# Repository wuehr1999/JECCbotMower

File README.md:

# JECCbotMower

Implementation of JECCbot modifications for lawn mowing robot

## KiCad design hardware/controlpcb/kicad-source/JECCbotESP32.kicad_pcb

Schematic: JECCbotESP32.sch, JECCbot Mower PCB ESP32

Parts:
C1: 100n; C_0603
C2, C3: 10uF; C_0603
C47: 100nF; C_0603
D1: Led_Small; LED_0603
R1, R3, R4, R5: 10k; R_0603
R2: 220; R_0603
R7: DNI; R_0603
SW1, SW2: TAST_VER; WE_430182050816
U1: ESP32_WROOM_32; ESP32-WROOM-32
U2, U3: 74xx4052; SOIC-16_3.9x9.9mm_Pitch1.27mm
U4: TCA9534; SOIC-16_7.5x10.3mm_Pitch1.27mm
U5: ADS1015; MSOP-10_3x3mm_Pitch0.5mm

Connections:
+3V3: C2.1, C3.1, C47.1, D1.2 (A), R1.1, R3.1, R4.1, R5.1, U1.2 (3V3), U2.16, U3.16, U4.16 (VCC), U5.8 (VCC); also elsewhere on the board
/INT: R5.2, U1.6 (IO34), U4.13 (INT)
/MUX1_A: U1.13 (IO14), U2.10
/MUX1_B: U1.14 (IO12), U2.9
/MUX2_A: U1.16 (IO13), U3.10
/MUX2_B: U1.23 (IO15), U3.9
/MUX2_COM1: U1.26 (IO4), U3.13
/MUX2_COM2: U1.7 (IO35), U3.3
/RX: U1.27 (IO16), U2.13
/TX: U1.28 (IO17), U2.3
ADC: U5.7 (AIN3); also elsewhere on the board
BOOT: SW1.1, SW1.3, U1.25 (IO0); also elsewhere on the board
CS: U4.4 (P0); also elsewhere on the board
DRIVE_BEMF1: U1.4 (SENSOR_VP); also elsewhere on the board
DRIVE_BEMF2: U1.5 (SENSOR_VN); also elsewhere on the board
DRIVE_INH: U1.12 (IO27); also elsewhere on the board
DRIVE_IS: U5.4 (AIN0); also elsewhere on the board
DRIVE_PWM1: U1.8 (IO32); also elsewhere on the board
DRIVE_PWM2: U1.9 (IO33); also elsewhere on the board
DRIVE_PWM3: U1.10 (IO25); also elsewhere on the board
DRIVE_PWM4: U1.11 (IO26); also elsewhere on the board
EM_STOP: U4.5 (P1); also elsewhere on the board
GND: C1.2, C2.2, C3.2, C47.2, R2.2, R7.2, SW1.2, SW1.4, SW2.2, SW2.4, U1.1 (GND), U1.15 (GND), U1.38 (GND), U1.39 (P_GND), U2.6, U2.7, U2.8, U3.6, U3.7, U3.8, U4.1 (A0), U4.2 (A1), U4.3 (A2), U4.8 (GND), U5.3 (GND); also elsewhere on the board
GPIO0: U4.9 (P4); also elsewhere on the board
GPIO1: U4.10 (P5); also elsewhere on the board
GPIO2: U4.11 (P6); also elsewhere on the board
GPIO3: U4.12 (P7); also elsewhere on the board
GPIO5: U1.29 (IO5); also elsewhere on the board
INT_BNO055: U4.7 (P3); also elsewhere on the board
KNIFE_INH: U4.6 (P2); also elsewhere on the board
KNIFE_IS: U5.5 (AIN1); also elsewhere on the board
KNIFE_PWM: U1.24 (IO2); also elsewhere on the board
MISO: U1.31 (IO19); also elsewhere on the board
MOSI: U1.37 (IO23); also elsewhere on the board
unnamed: D1.1 (K), R2.1
unnamed: R7.1, U5.1 (ADDR)
RESET: C1.1, R1.2, SW2.1, SW2.3, U1.3 (EN); also elsewhere on the board
RX0: U2.12; also elsewhere on the board
RX0_USB: U1.34 (RXD0); also elsewhere on the board
RX1: U2.14; also elsewhere on the board
RX2: U2.15; also elsewhere on the board
RX3: U2.11; also elsewhere on the board
SCK: U1.30 (IO18); also elsewhere on the board
SCL: R4.2, U1.36 (IO22), U4.14 (SCL), U5.10 (SCL); also elsewhere on the board
SDA: R3.2, U1.33 (IO21), U4.15 (SDA), U5.9 (SDA); also elsewhere on the board
TX0: U2.1; also elsewhere on the board
TX0_USB: U1.35 (TXD0); also elsewhere on the board
TX1: U2.5; also elsewhere on the board
TX2: U2.2; also elsewhere on the board
TX3: U2.4; also elsewhere on the board
U1_ECHO: U3.1; also elsewhere on the board
U1_TRIG: U3.12; also elsewhere on the board
U2_ECHO: U3.5; also elsewhere on the board
U2_TRIG: U3.14; also elsewhere on the board
U3_ECHO: U3.2; also elsewhere on the board
U3_TRIG: U3.15; also elsewhere on the board
VBAT_SENSE: U5.6 (AIN2); also elsewhere on the board

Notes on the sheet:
onboard flash

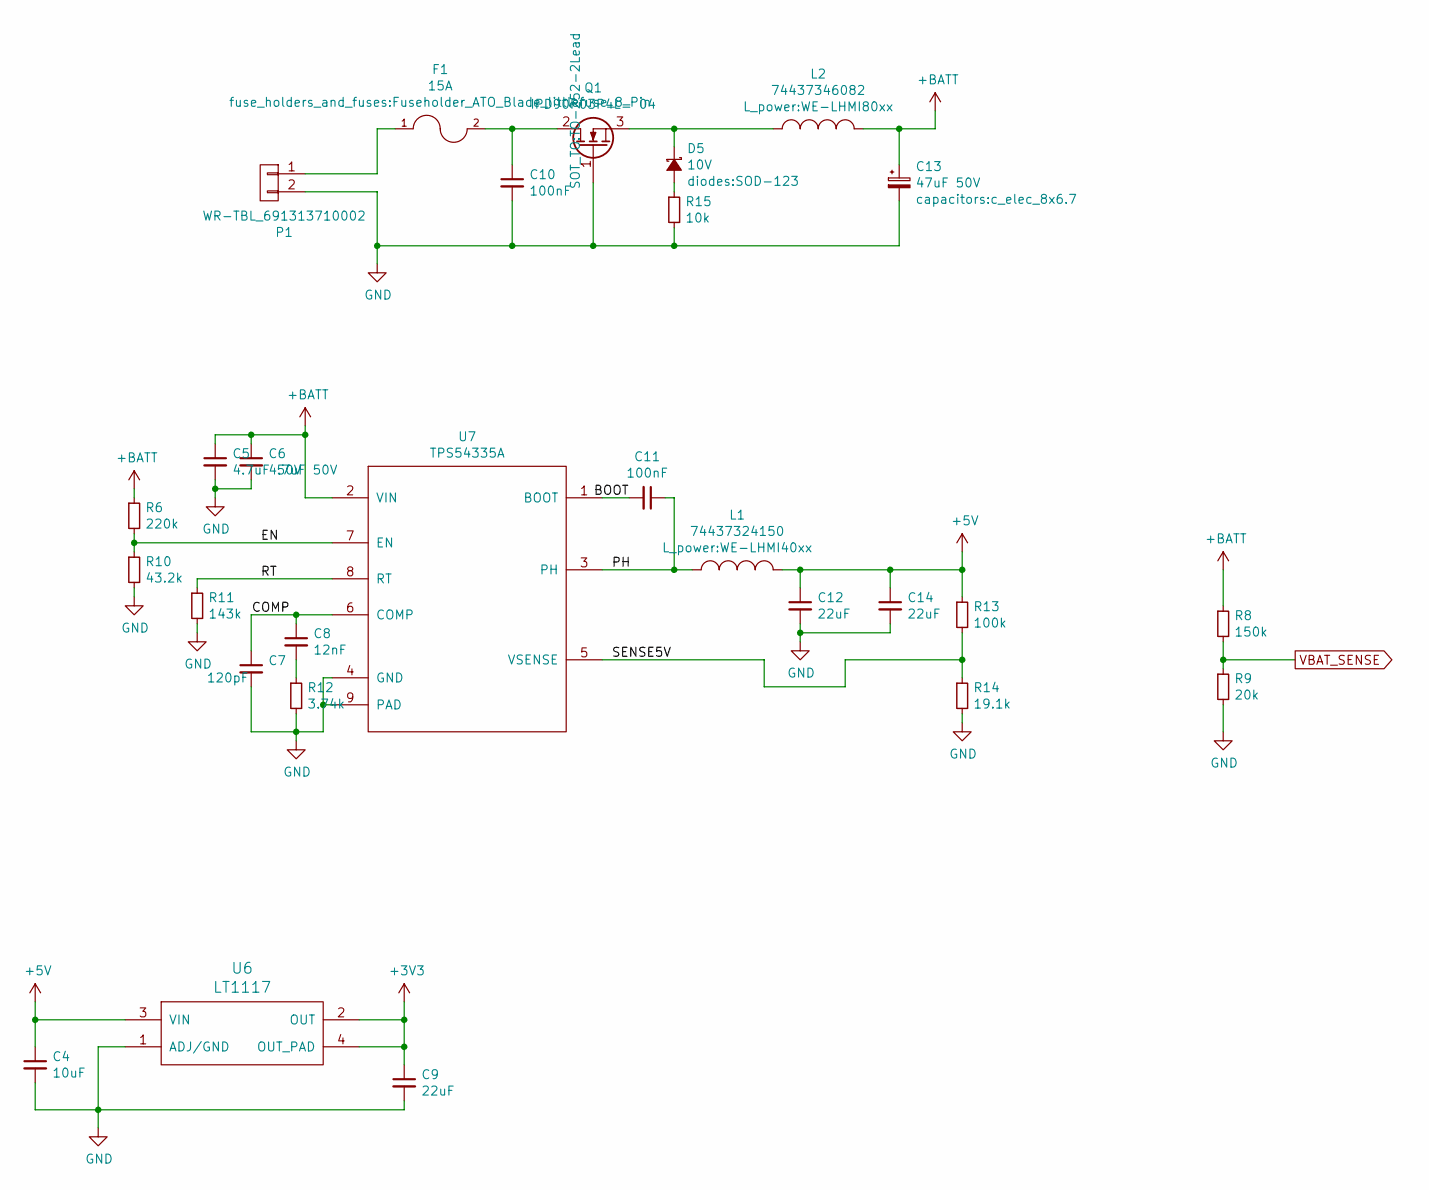
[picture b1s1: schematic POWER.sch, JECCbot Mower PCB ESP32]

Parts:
C4: 10uF; C_1206
C5, C6: 4.7uF 50V; C_1206
C7: 120pF; C_0603
C8: 12nF; C_0603
C9, C12, C14: 22uF; C_1206
C10, C11: 100nF; C_0603
C13: 47uF 50V; c_elec_8x6.7
D5: 10V; SOD-123
F1: 15A; Fuseholder_ATO_Blade_littlefuse_8_Pin
L1: 74437324150; WE-LHMI40xx
L2: 74437346082; WE-LHMI80xx
P1: WR-TBL_691313710002
Q1: IPD90P03P4L- 04; TO-252-2Lead
R6: 220k; R_0603
R8: 150k; R_0603
R9: 20k; R_0603
R10: 43.2k; R_0603
R11: 143k; R_0603
R12: 3.74k; R_0603
R13: 100k; R_0603
R14: 19.1k; R_0603
R15: 10k; R_0603
U6: LT1117; SOT-223
U7: TPS54335A; SOIC-8-1EP_3.9x4.9mm_Pitch1.27mm

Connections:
+3V3: C9.1, U6.2 (OUT), U6.4 (OUT_PAD); also elsewhere on the board
+5V: C4.1, C12.1, C14.1, L1.2, R13.1, U6.3 (VIN); also elsewhere on the board
+BATT: C5.1, C6.1, C13.1, L2.2, R6.1, R8.1, U7.2 (VIN); also elsewhere on the board
/POWER/COMP: C7.1, C8.1, U7.6 (COMP)
/POWER/EN: R6.2, R10.1, U7.7 (EN)
/POWER/PH: C11.1, L1.1, U7.3 (PH)
/POWER/RT: R11.1, U7.8 (RT)
/POWER/SENSE5V: R13.2, R14.1, U7.5 (VSENSE)
GND: C4.2, C5.2, C6.2, C7.2, C9.2, C10.2, C12.2, C13.2, C14.2, P1.2, Q1.1 (G), R9.2, R10.2, R11.2, R12.2, R14.2, R15.2, U6.1 (ADJ/GND), U7.4 (GND), U7.9 (PAD); also elsewhere on the board
unnamed: C8.2, R12.1
unnamed: C10.1, F1.2, Q1.2 (D)
unnamed: C11.2, U7.1 (BOOT)
unnamed: D5.1 (K), L2.1, Q1.3 (S)
unnamed: D5.2 (A), R15.1
unnamed: F1.1, P1.1
VBAT_SENSE: R8.2, R9.1; also elsewhere on the board

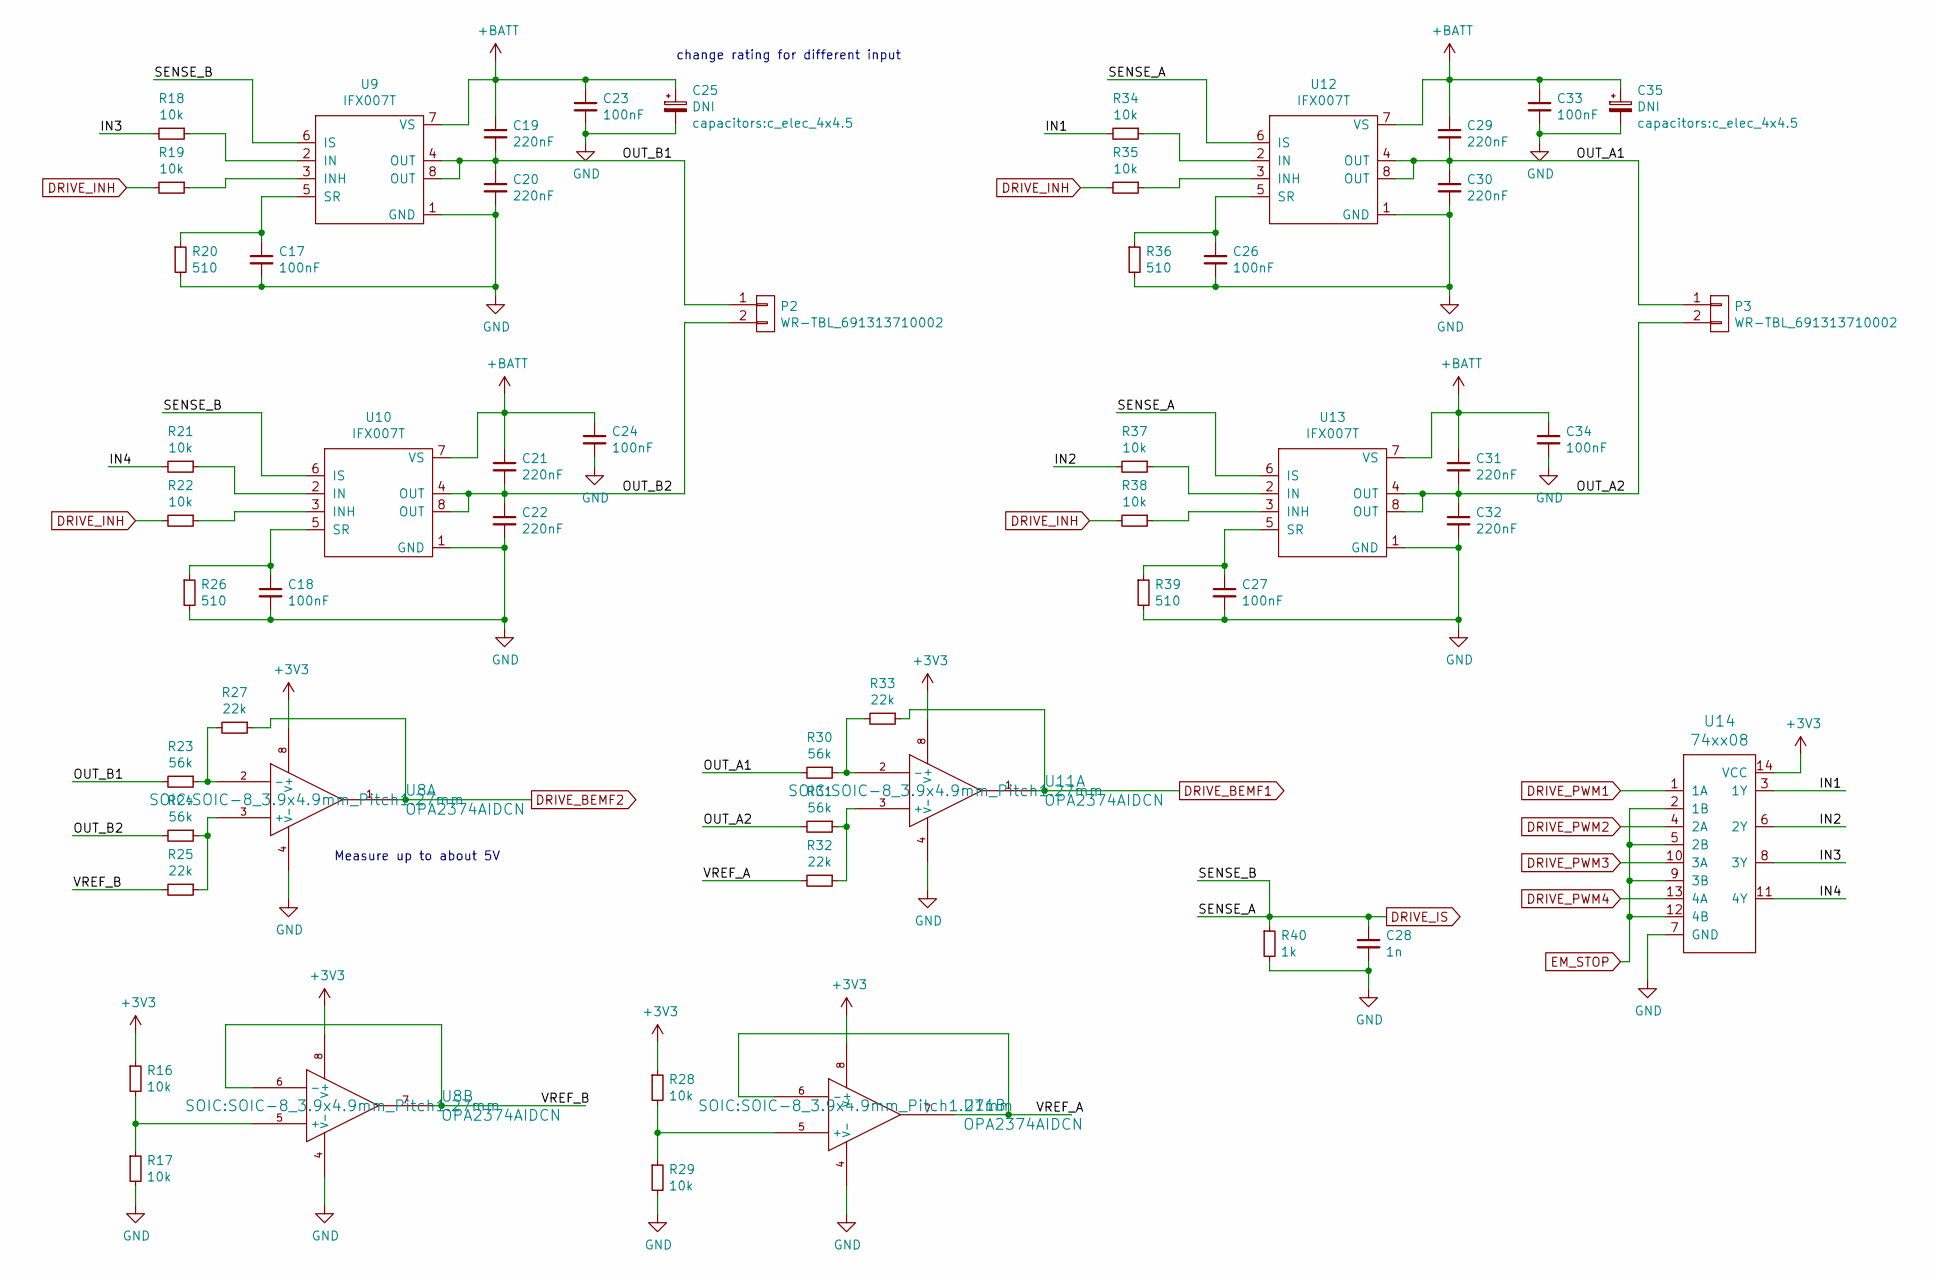
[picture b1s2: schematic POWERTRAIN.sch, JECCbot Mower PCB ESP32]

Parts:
C17, C18, C23, C24, C26, C27, C33, C34: 100nF; C_0603
C19, C20, C21, C22, C29, C30, C31, C32: 220nF; C_0603
C25, C35: DNI; c_elec_4x4.5
C28: 1n; C_0603
P2, P3: WR-TBL_691313710002
R16, R17, R18, R19, R21, R22, R28, R29, R34, R35, R37, R38: 10k; R_0603
R20, R26, R36, R39: 510; R_0603
R23, R24, R30, R31: 56k; R_0603
R25, R27, R32, R33: 22k; R_0603
R40: 1k; R_0603
U8, U11: OPA2374AIDCN; SOIC-8_3.9x4.9mm_Pitch1.27mm
U9, U10, U12, U13: IFX007T; TO-263-7Lead
U14: 74xx08; SOIC-14_3.9x8.7mm_Pitch1.27mm

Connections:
+3V3: R16.1, R28.1, U8.8 (V+), U11.8 (V+), U14.14 (VCC); also elsewhere on the board
+BATT: C19.1, C21.1, C23.1, C24.1, C25.1, C29.1, C31.1, C33.1, C34.1, C35.1, U9.7 (VS), U10.7 (VS), U12.7 (VS), U13.7 (VS); also elsewhere on the board
/POWERTRAIN/IN1: R34.2, U14.3 (1Y)
/POWERTRAIN/IN2: R37.2, U14.6 (2Y)
/POWERTRAIN/IN3: R18.2, U14.8 (3Y)
/POWERTRAIN/IN4: R21.2, U14.11 (4Y)
/POWERTRAIN/OUT_A1: C29.2, C30.1, P3.1, R30.2, U12.4 (OUT), U12.8 (OUT)
/POWERTRAIN/OUT_A2: C31.2, C32.1, P3.2, R31.2, U13.4 (OUT), U13.8 (OUT)
/POWERTRAIN/OUT_B1: C19.2, C20.1, P2.1, R23.2, U9.4 (OUT), U9.8 (OUT)
/POWERTRAIN/OUT_B2: C21.2, C22.1, P2.2, R24.2, U10.4 (OUT), U10.8 (OUT)
/POWERTRAIN/VREF_A: R32.2, U11.6 (-), U11.7
/POWERTRAIN/VREF_B: R25.2, U8.6 (-), U8.7
DRIVE_BEMF1: R33.1, U11.1; also elsewhere on the board
DRIVE_BEMF2: R27.1, U8.1; also elsewhere on the board
DRIVE_INH: R19.2, R22.2, R35.2, R38.2; also elsewhere on the board
DRIVE_IS: C28.1, R40.1, U9.6 (IS), U10.6 (IS), U12.6 (IS), U13.6 (IS); also elsewhere on the board
DRIVE_PWM1: U14.1 (1A); also elsewhere on the board
DRIVE_PWM2: U14.4 (2A); also elsewhere on the board
DRIVE_PWM3: U14.10 (3A); also elsewhere on the board
DRIVE_PWM4: U14.13 (4A); also elsewhere on the board
EM_STOP: U14.2 (1B), U14.5 (2B), U14.9 (3B), U14.12 (4B); also elsewhere on the board
GND: C17.2, C18.2, C20.2, C22.2, C23.2, C24.2, C25.2, C26.2, C27.2, C28.2, C30.2, C32.2, C33.2, C34.2, C35.2, R17.2, R20.2, R26.2, R29.2, R36.2, R39.2, R40.2, U8.4 (V-), U9.1 (GND), U10.1 (GND), U11.4 (V-), U12.1 (GND), U13.1 (GND), U14.7 (GND); also elsewhere on the board
unnamed: C17.1, R20.1, U9.5 (SR)
unnamed: C18.1, R26.1, U10.5 (SR)
unnamed: C26.1, R36.1, U12.5 (SR)
unnamed: C27.1, R39.1, U13.5 (SR)
unnamed: R16.2, R17.1, U8.5 (+)
unnamed: R18.1, U9.2 (IN)
unnamed: R19.1, U9.3 (INH)
unnamed: R21.1, U10.2 (IN)
unnamed: R22.1, U10.3 (INH)
unnamed: R23.1, R27.2, U8.2 (-)
unnamed: R24.1, R25.1, U8.3 (+)
unnamed: R28.2, R29.1, U11.5 (+)
unnamed: R30.1, R33.2, U11.2 (-)
unnamed: R31.1, R32.1, U11.3 (+)
unnamed: R34.1, U12.2 (IN)
unnamed: R35.1, U12.3 (INH)
unnamed: R37.1, U13.2 (IN)
unnamed: R38.1, U13.3 (INH)

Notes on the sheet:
Measure up to about 5V
change rating for different input

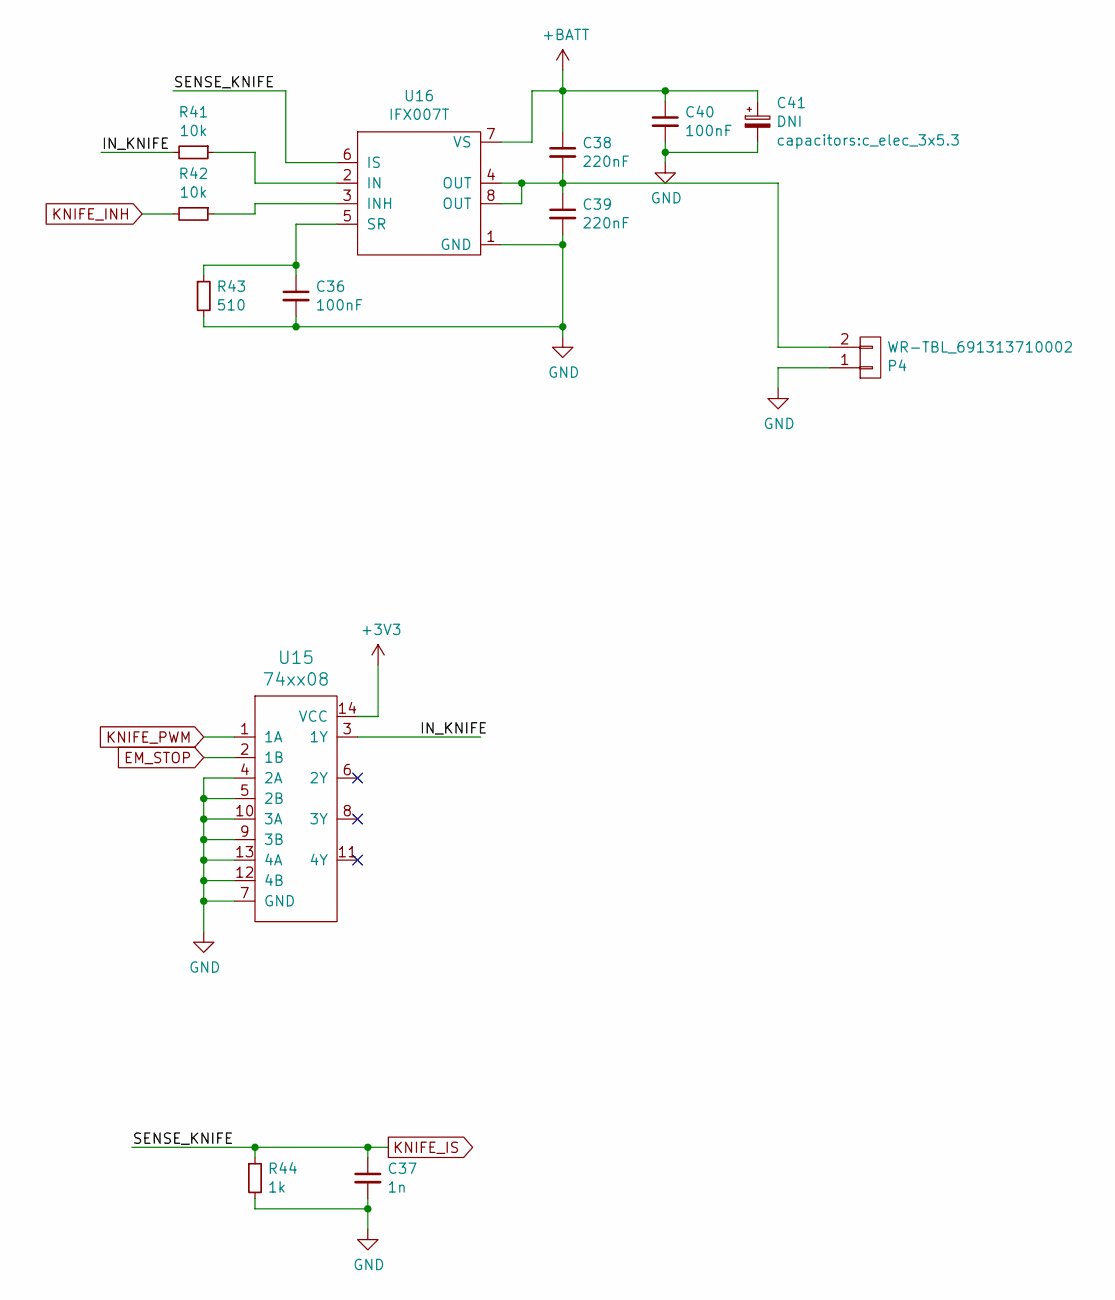
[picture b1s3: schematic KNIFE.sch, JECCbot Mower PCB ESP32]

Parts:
C36, C40: 100nF; C_0603
C37: 1n; C_0603
C38, C39: 220nF; C_0603
C41: DNI; c_elec_3x5.3
P4: WR-TBL_691313710002
R41, R42: 10k; R_0603
R43: 510; R_0603
R44: 1k; R_0603
U15: 74xx08; SOIC-14_3.9x8.7mm_Pitch1.27mm
U16: IFX007T; TO-263-7Lead

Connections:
+3V3: U15.14 (VCC); also elsewhere on the board
+BATT: C38.1, C40.1, C41.1, U16.7 (VS); also elsewhere on the board
/KNIFE/IN_KNIFE: R41.2, U15.3 (1Y)
EM_STOP: U15.2 (1B); also elsewhere on the board
GND: C36.2, C37.2, C39.2, C40.2, C41.2, P4.1, R43.2, R44.2, U15.4 (2A), U15.5 (2B), U15.7 (GND), U15.9 (3B), U15.10 (3A), U15.12 (4B), U15.13 (4A), U16.1 (GND); also elsewhere on the board
KNIFE_INH: R42.2; also elsewhere on the board
KNIFE_IS: C37.1, R44.1, U16.6 (IS); also elsewhere on the board
KNIFE_PWM: U15.1 (1A); also elsewhere on the board
unnamed: C36.1, R43.1, U16.5 (SR)
unnamed: C38.2, C39.1, P4.2, U16.4 (OUT), U16.8 (OUT)
unnamed: R41.1, U16.2 (IN)
unnamed: R42.1, U16.3 (INH)

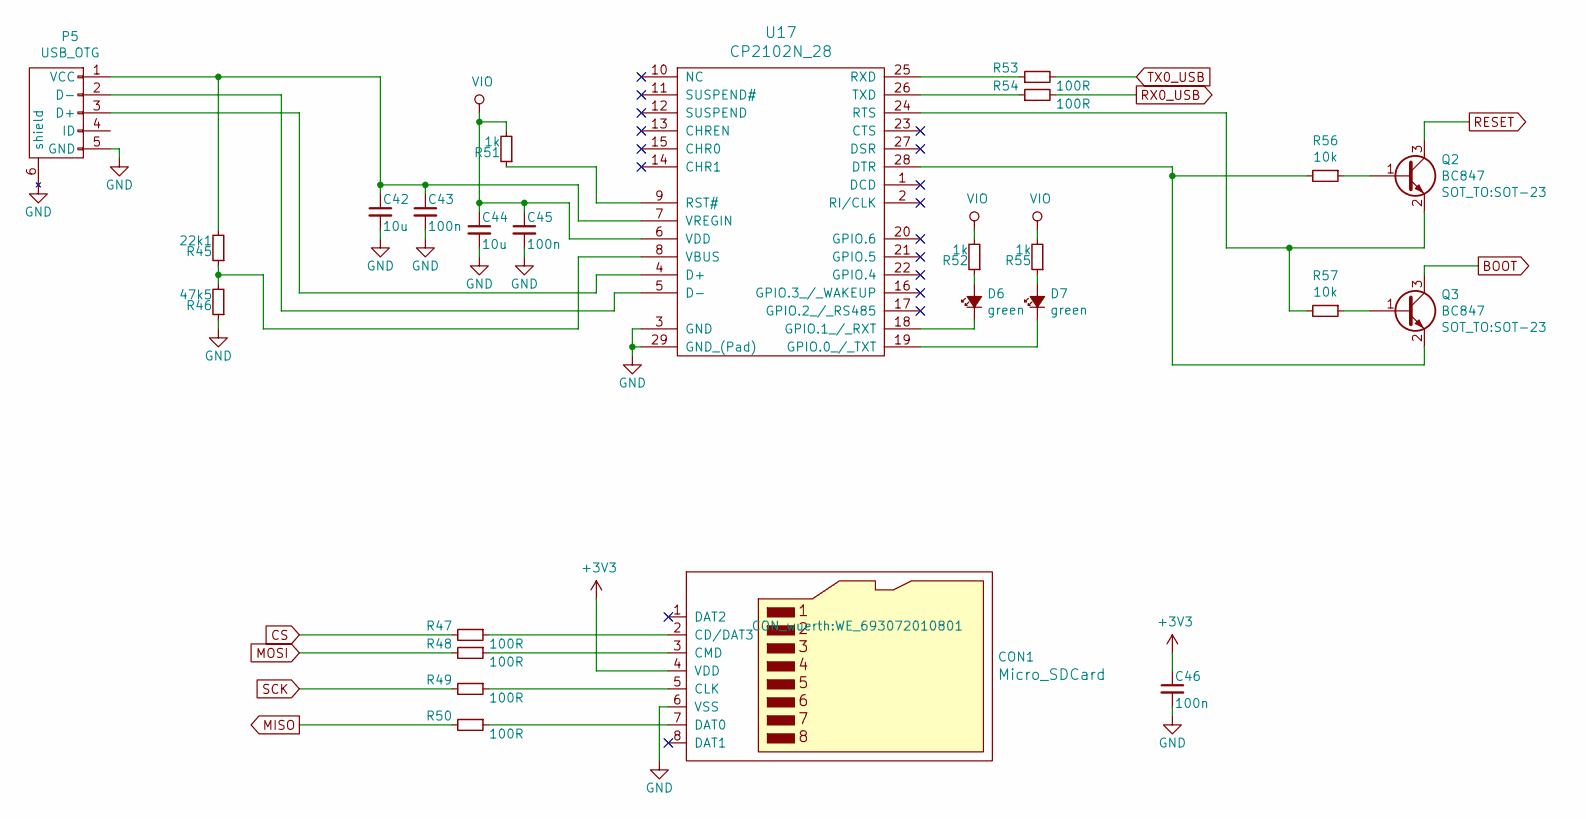
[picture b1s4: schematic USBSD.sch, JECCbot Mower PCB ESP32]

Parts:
C42, C44: 10u; C_0603
C43, C45, C46: 100n; C_0603
CON1: Micro_SDCard; WE_693072010801
D6, D7: green; LED_0603
P5: USB_OTG; USB_Micro-B
Q2, Q3: BC847; SOT-23
R45: 22k1; R_0603
R46: 47k5; R_0603
R47, R48, R49, R50, R53, R54: 100R; R_0603
R51, R52, R55: 1k; R_0603
R56, R57: 10k; R_0603
U17: CP2102N_28; QFN-28-1EP_5x5mm_Pitch0.5mm

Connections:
+3V3: C46.1, CON1.4 (VDD); also elsewhere on the board
BOOT: Q3.3 (C); also elsewhere on the board
CS: R47.2; also elsewhere on the board
GND: C42.2, C43.2, C44.2, C45.2, C46.2, CON1.6 (VSS), P5.5 (GND), P5.6 (shield), R46.1, U17.3 (GND), U17.29 (GND_(Pad)); also elsewhere on the board
MISO: R50.2; also elsewhere on the board
MOSI: R48.2; also elsewhere on the board
unnamed: C42.1, C43.1, P5.1 (VCC), R45.2, U17.7 (VREGIN)
unnamed: CON1.2 (CD/DAT3), R47.1
unnamed: CON1.3 (CMD), R48.1
unnamed: CON1.5 (CLK), R49.1
unnamed: CON1.7 (DAT0), R50.1
unnamed: D6.1 (K), U17.18 (GPIO.1_/_RXT)
unnamed: D6.2 (A), R52.1
unnamed: D7.1 (K), U17.19 (GPIO.0_/_TXT)
unnamed: D7.2 (A), R55.1
unnamed: P5.2 (D-), U17.5 (D-)
unnamed: P5.3 (D+), U17.4 (D+)
unnamed: Q2.1 (B), R56.1
unnamed: Q2.2 (E), R57.2, U17.24 (RTS)
unnamed: Q3.1 (B), R57.1
unnamed: Q3.2 (E), R56.2, U17.28 (DTR)
unnamed: R45.1, R46.2, U17.8 (VBUS)
unnamed: R51.1, U17.9 (RST#)
unnamed: R53.1, U17.25 (RXD)
unnamed: R54.1, U17.26 (TXD)
RESET: Q2.3 (C); also elsewhere on the board
RX0_USB: R54.2; also elsewhere on the board
SCK: R49.2; also elsewhere on the board
TX0_USB: R53.2; also elsewhere on the board
VIO: C44.1, C45.1, R51.2, R52.2, R55.2, U17.6 (VDD)

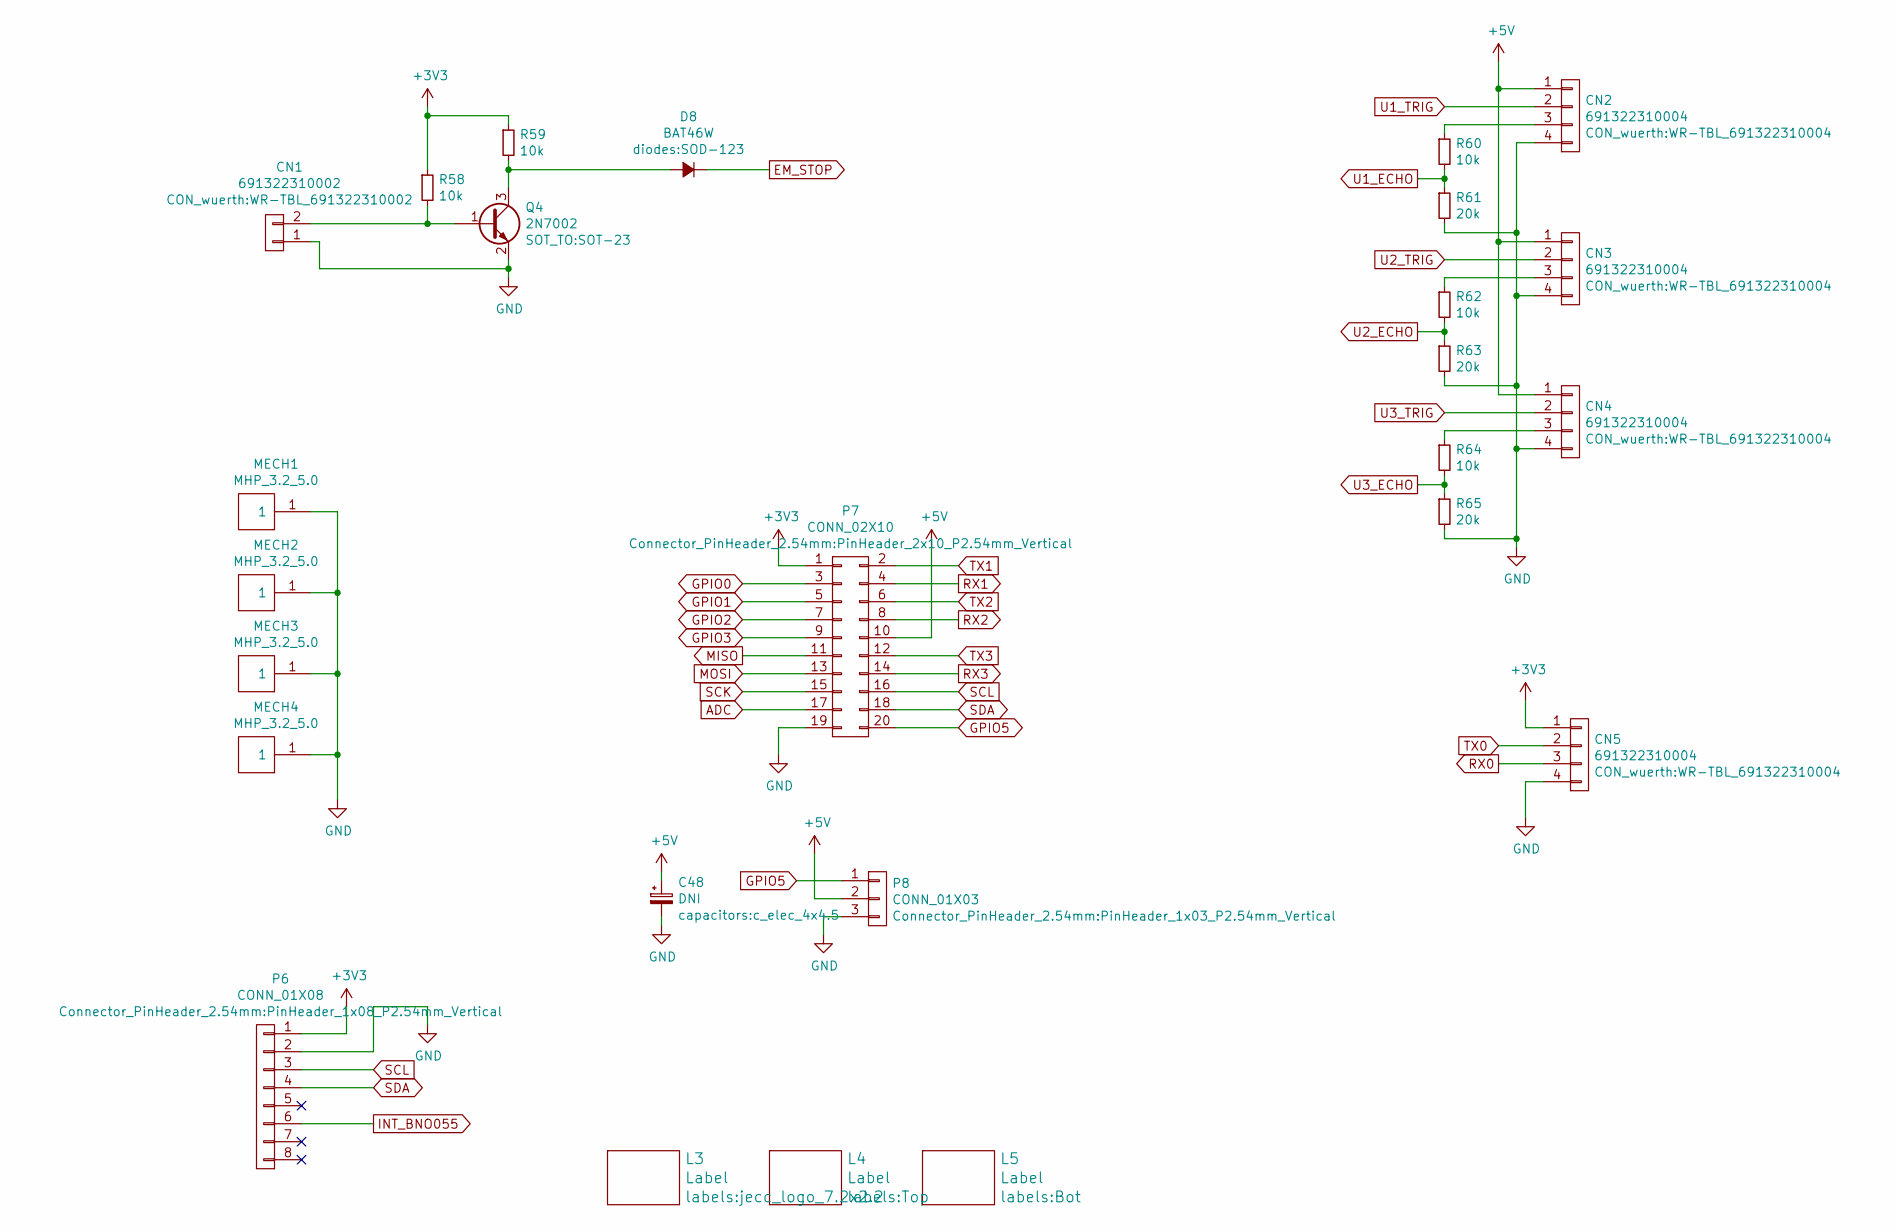
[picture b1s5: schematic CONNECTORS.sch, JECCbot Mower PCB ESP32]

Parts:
C48: DNI; c_elec_4x4.5
CN1: 691322310002; WR-TBL_691322310002
CN2, CN3, CN4, CN5: 691322310004; WR-TBL_691322310004
D8: BAT46W; SOD-123
L3: Label; jecc_logo_7.2x2.2
L4: Label; Top
L5: Label; Bot
MECH1, MECH2, MECH3, MECH4: MHP_3.2_5.0
P6: CONN_01X08; PinHeader_1x08_P2.54mm_Vertical
P7: CONN_02X10; PinHeader_2x10_P2.54mm_Vertical
P8: CONN_01X03; PinHeader_1x03_P2.54mm_Vertical
Q4: 2N7002; SOT-23
R58, R59, R60, R62, R64: 10k; R_0603
R61, R63, R65: 20k; R_0603

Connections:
+3V3: CN5.1, P6.1, P7.1, R58.1, R59.1; also elsewhere on the board
+5V: C48.1, CN2.1, CN3.1, CN4.1, P7.10, P8.2; also elsewhere on the board
ADC: P7.17; also elsewhere on the board
EM_STOP: D8.1 (K); also elsewhere on the board
GND: C48.2, CN1.1, CN2.4, CN3.4, CN4.4, CN5.4, MECH1.1, MECH2.1, MECH3.1, MECH4.1, P6.2, P7.19, P8.3, Q4.2 (E), R61.2, R63.2, R65.2; also elsewhere on the board
GPIO0: P7.3; also elsewhere on the board
GPIO1: P7.5; also elsewhere on the board
GPIO2: P7.7; also elsewhere on the board
GPIO3: P7.9; also elsewhere on the board
GPIO5: P7.20, P8.1; also elsewhere on the board
INT_BNO055: P6.6; also elsewhere on the board
MISO: P7.11; also elsewhere on the board
MOSI: P7.13; also elsewhere on the board
unnamed: CN1.2, Q4.1 (B), R58.2
unnamed: CN2.3, R60.1
unnamed: CN3.3, R62.1
unnamed: CN4.3, R64.1
unnamed: D8.2 (A), Q4.3 (C), R59.2
RX0: CN5.3; also elsewhere on the board
RX1: P7.4; also elsewhere on the board
RX2: P7.8; also elsewhere on the board
RX3: P7.14; also elsewhere on the board
SCK: P7.15; also elsewhere on the board
SCL: P6.3, P7.16; also elsewhere on the board
SDA: P6.4, P7.18; also elsewhere on the board
TX0: CN5.2; also elsewhere on the board
TX1: P7.2; also elsewhere on the board
TX2: P7.6; also elsewhere on the board
TX3: P7.12; also elsewhere on the board
U1_ECHO: R60.2, R61.1; also elsewhere on the board
U1_TRIG: CN2.2; also elsewhere on the board
U2_ECHO: R62.2, R63.1; also elsewhere on the board
U2_TRIG: CN3.2; also elsewhere on the board
U3_ECHO: R64.2, R65.1; also elsewhere on the board
U3_TRIG: CN4.2; also elsewhere on the board

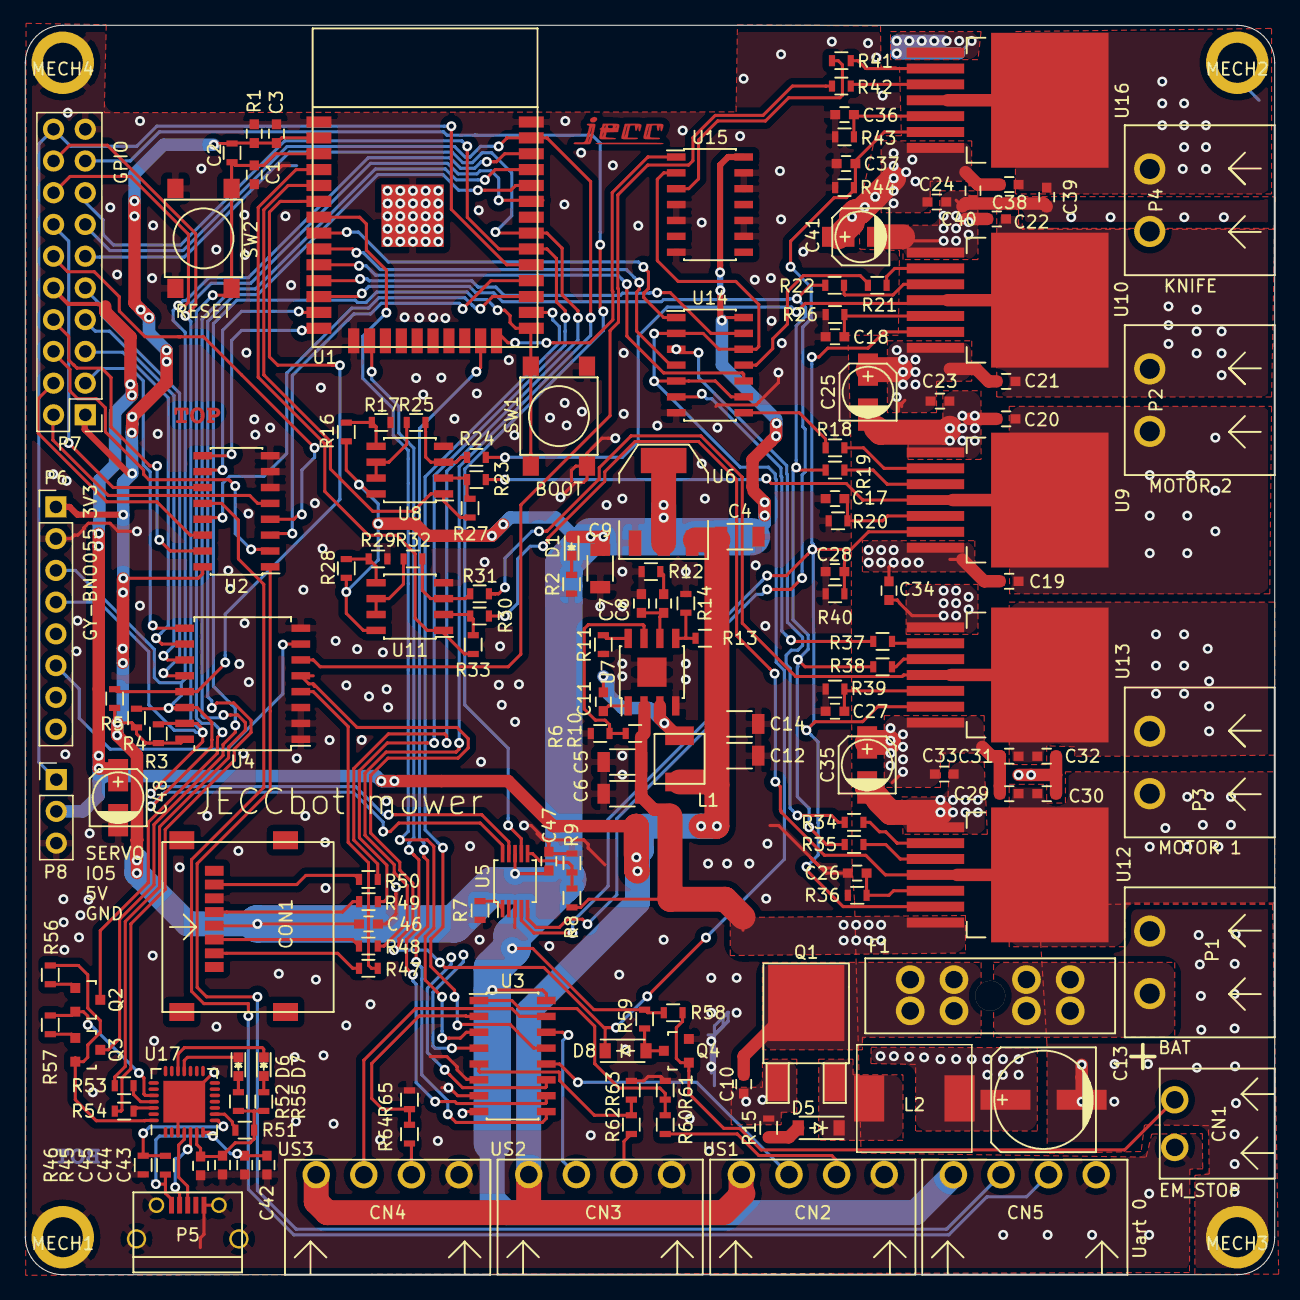
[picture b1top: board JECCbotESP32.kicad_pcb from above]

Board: 2 copper layers, 100.0 x 100.0 mm, 163 parts (0 on the bottom side), 128 nets.

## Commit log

2020-05-28 added kicad source
2020-05-28 added 3dview
2020-05-29 added rendering and schematics pdf
2020-05-30 added servo connector
2020-06-02 changed layout
2020-06-05 changed power supply
2020-06-05 changed ground plane
2020-06-06 finally
2020-06-06 changed powertrace
